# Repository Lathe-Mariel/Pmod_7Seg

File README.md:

# Pmod_7Seg
6桁7セグLEDを載せたPmod基板．  
Pmodを2ポート使う

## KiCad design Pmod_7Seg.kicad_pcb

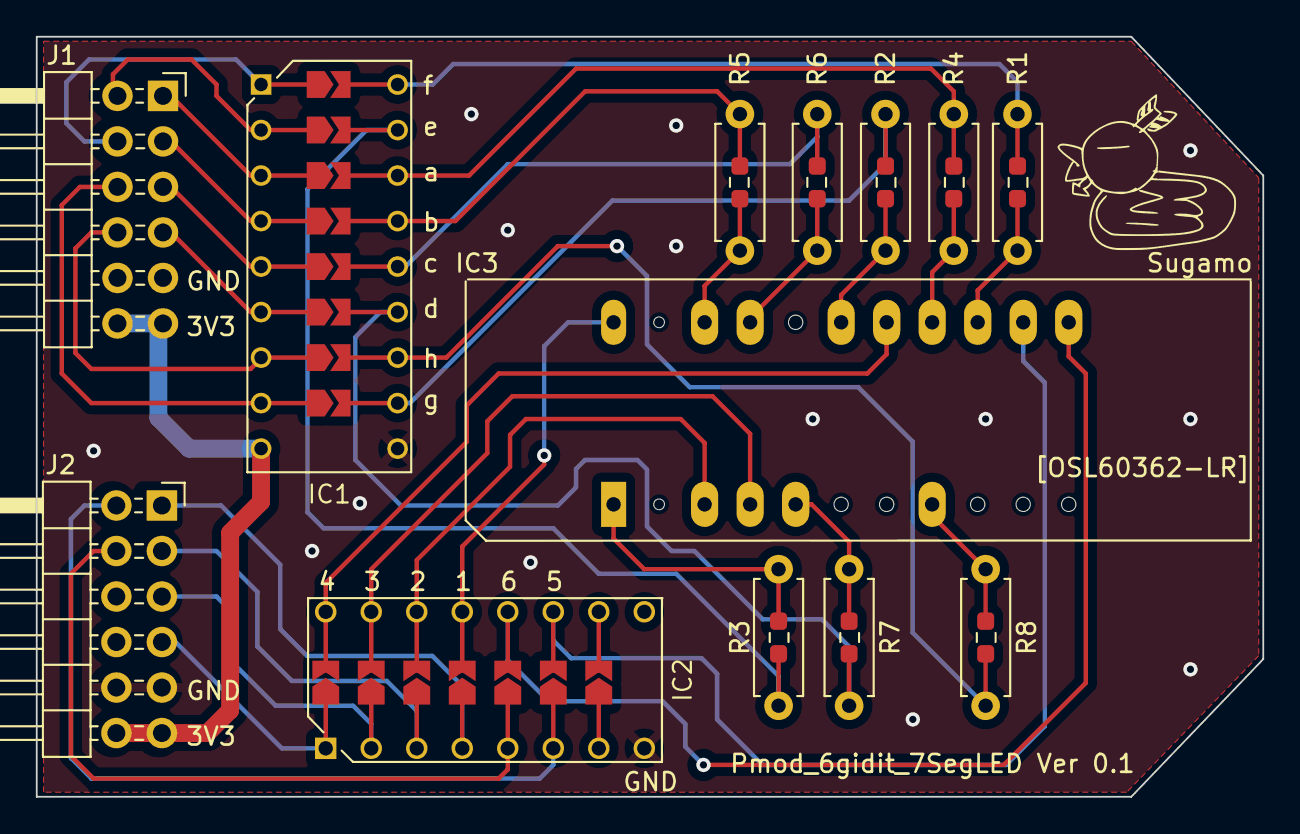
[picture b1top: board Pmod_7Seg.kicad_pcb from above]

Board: 2 copper layers, 68.5 x 42.4 mm, 13 parts (0 on the bottom side), 38 nets.

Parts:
IC1: TBD62783APG; DIP762W55P254L2286H480Q18N_with_solderjumper
IC2: TBD62003APG; DIP762W60P254L1975H445Q16N_solderjumper
IC3: OSL60362-LR; OSL60362-LR-with-allpin
J1, J2: Conn_02x06_Counter_Clockwise; Pmod
R1, R2, R3, R4, R5, R6, R7, R8: 68; Resistor_SMD_THT

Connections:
GND: IC1.10 (GND), IC2.8 (GND), J1.5, J1.11, J2.5, J2.11
unnamed: IC3.15 (ANODE_A), R4.1
unnamed: IC3.20 (ANODE_B), R5.2
unnamed: IC3.19 (ANODE_C), R6.2
unnamed: IC3.5 (ANODE_D), R7.2
unnamed: IC3.8 (ANODE_DP), R8.2
unnamed: IC3.1 (ANODE_E), R3.2
unnamed: IC3.14 (ANODE_F), R1.1
unnamed: IC3.17 (ANODE_G), R2.1
unnamed: IC2.13 (O4), IC3.22 (KATHODE_1)
unnamed: IC2.14 (O3), IC3.3 (KATHODE_2)
unnamed: IC2.15 (O2), IC3.4 (KATHODE_3)
unnamed: IC2.16 (O1), IC3.16 (KATHODE_4)
unnamed: IC2.11 (O6), IC3.13 (KATHODE_5)
unnamed: IC2.12 (O5), IC3.12 (KATHODE_6)
unnamed: IC1.1 (I1), J1.8
unnamed: IC1.2 (I2), J1.7
unnamed: IC1.3 (I3), J1.1
unnamed: IC1.4 (I4), J1.2
unnamed: IC1.5 (I5), J1.3
unnamed: IC1.6 (I6), J1.4
unnamed: IC1.7 (I7), J1.10
unnamed: IC1.8 (I8), J1.9
unnamed: IC1.18 (O1), R1.2
unnamed: IC1.17 (O2), R3.1
unnamed: IC1.16 (O3), R4.2
unnamed: IC1.15 (O4), R5.1
unnamed: IC1.14 (O5), R6.1
unnamed: IC1.13 (O6), R7.1
unnamed: IC1.12 (O7), R8.1
unnamed: IC1.11 (O8), R2.2
unnamed: IC2.4 (I4), J2.1
unnamed: IC2.3 (I3), J2.2
unnamed: IC2.2 (I2), J2.3
unnamed: IC2.1 (I1), J2.4
unnamed: IC2.6 (I6), J2.7
unnamed: IC2.5 (I5), J2.8
VCC: IC1.9 (VCC), J1.6, J1.12, J2.6, J2.12

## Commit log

2023-05-13 README.md
